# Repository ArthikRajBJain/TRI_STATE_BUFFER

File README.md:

# TRI_STATE_BUFFER
Tri state buffer to convert full duplex to half duplex

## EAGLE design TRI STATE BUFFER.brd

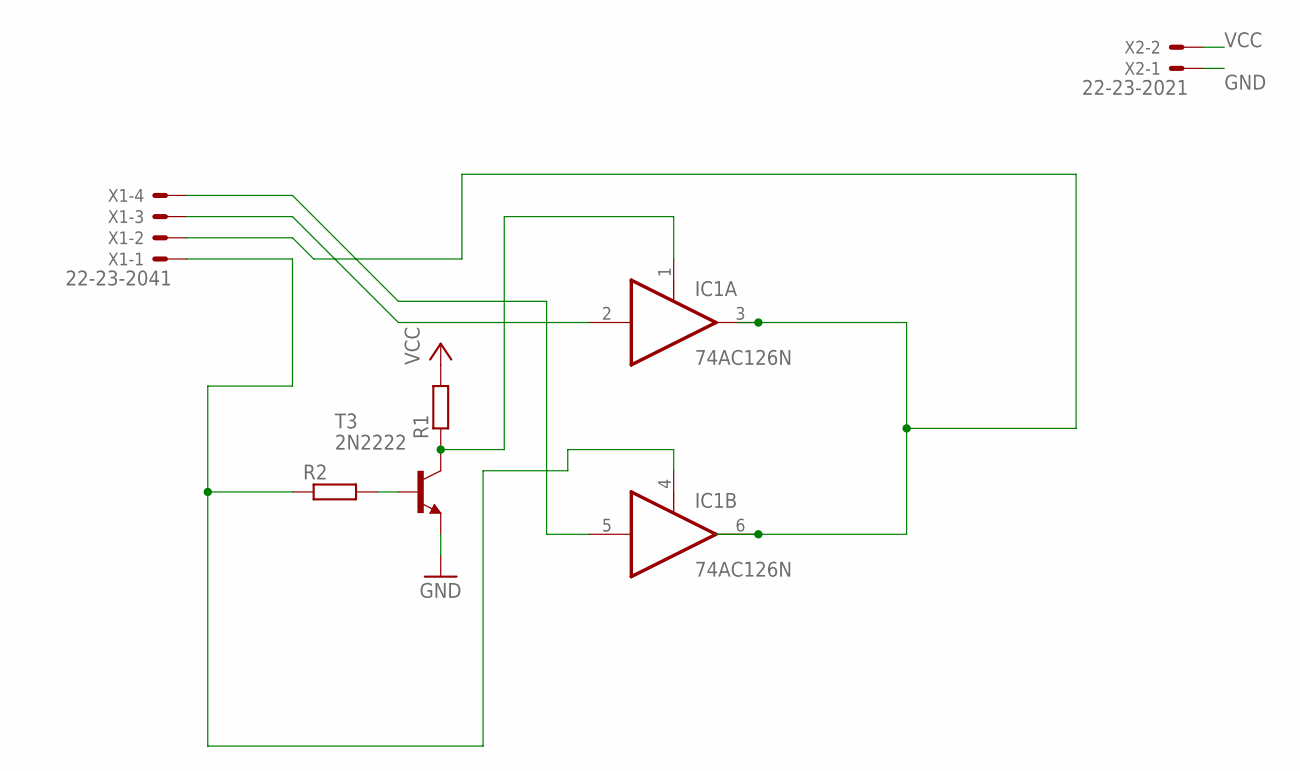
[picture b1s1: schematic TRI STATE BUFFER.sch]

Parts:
IC1: 74AC126N; DIL14
R1, R2: R0204/7; 0204/7
T3: 2N2222; TO92-EBC-OVAL
X1: 22-23-2041
X2: 22-23-2021

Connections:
GND: IC1.7 (GND), T3.E, X2.1
unnamed: IC1.1 (OE), R1.1, T3.C
unnamed: IC1.4 (OE), R2.1, X1.1
unnamed: IC1.3 (O), IC1.6 (O), X1.2
unnamed: IC1.5 (I), X1.4
unnamed: IC1.2 (I), X1.3
unnamed: R2.2, T3.B
VCC: IC1.14 (VCC), R1.2, X2.2

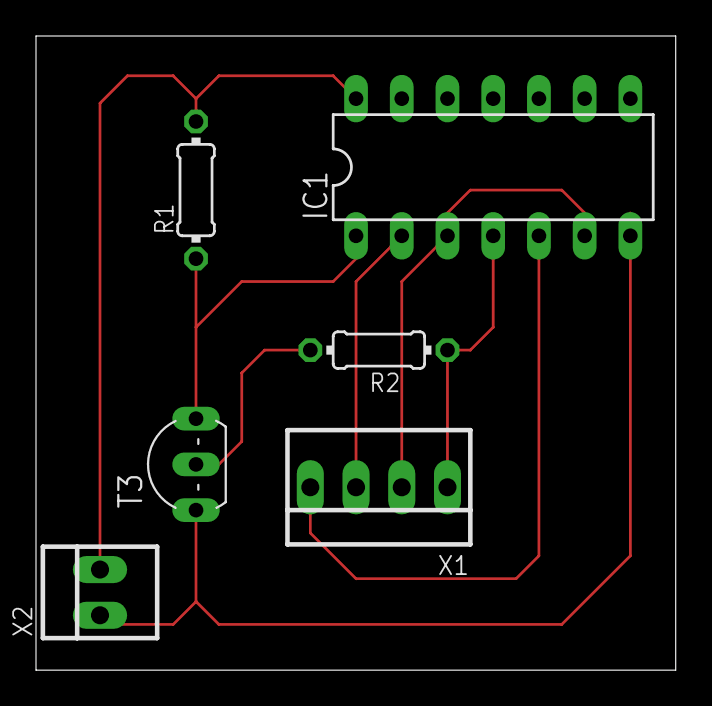
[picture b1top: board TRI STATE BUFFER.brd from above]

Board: 2 copper layers, 35.5 x 35.2 mm, 6 parts (0 on the bottom side), 8 nets.
